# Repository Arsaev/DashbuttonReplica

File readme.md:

**Dashbutton Replica** 
its a open source replica of IoT wifi button from Amazon

PCB and circuit in Eagle Project format

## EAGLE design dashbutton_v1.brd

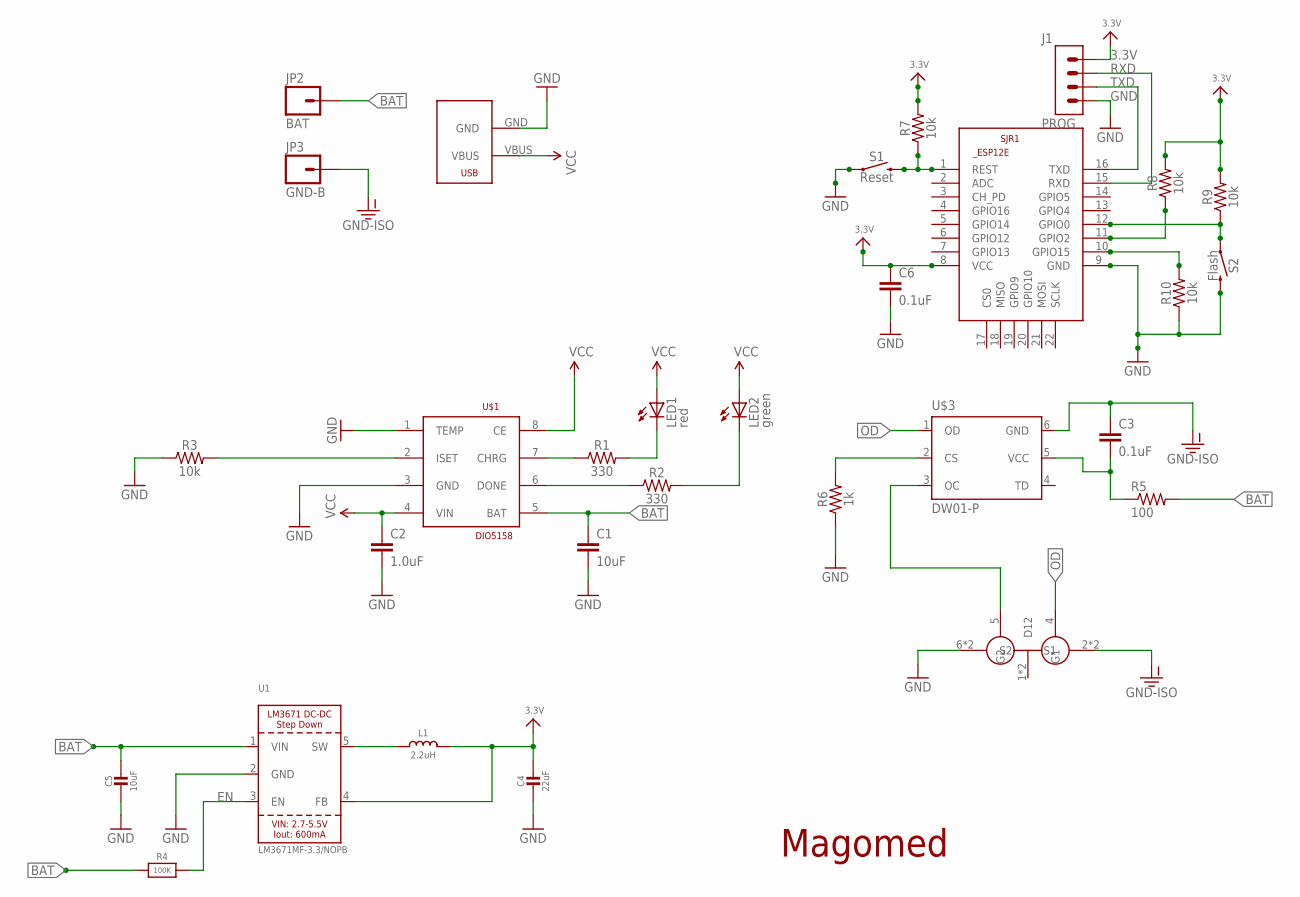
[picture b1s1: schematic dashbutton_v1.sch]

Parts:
C1: 10uF; 1206
C2: 1.0uF; 0603
C3, C6: 0.1uF; 0603
C4: 22uF; 0805-NO
C5: 10uF; 0805-NO
J1: PROG; 62000411121
JP2: BAT; 1X01
JP3: GND-B; 1X01
L1: 2.2uH; INDUCTOR_TAIYOYUDEN_NRH2412T
LED1: red; CHIP-LED0805
LED2: green; CHIP-LED0805
R1, R2: 330; 0603
R3, R7, R8, R9, R10: 10k; 0603
R4: 100K; 0805-NO
R5: 100; 0603-RES
R6: 1k; 0603
S1: Reset; TACTILE_SWITCH_SMD_6.2MM_TALL
S2: Flash; TACTILE_SWITCH_SMD_6.2MM_TALL
SJR1: ESP8266-12EESP12E; ESP8266-ESP12E
U1: LM3671MF-3.3/NOPB; SOT23-5
U$1: DIO5158; SOIC-8
U$3: DW01-P; SOT23-6L
U$4: FS8205A; TSSOP8
U$5: USB-MICROB-POWERONLY

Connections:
3.3V: C4.1, C6.1, J1.1, L1.2, R7.2, R8.2, R9.2, SJR1.8 (VCC), U1.4 (FB)
BAT: C1.1, C5.1, JP2.1, R4.1, R5.2, U1.1 (VIN), U$1.5 (BAT)
CHRG: R1.1, U$1.7 (CHRG)
DONE: R2.1, U$1.6 (DONE)
EN: R4.2, U1.3 (EN)
GND: C1.2, C2.2, C4.2, C5.2, C6.2, J1.4, R3.1, R6.1, R10.1, S1.A2 (1), S2.B2 (2), SJR1.9 (GND), U1.2 (GND), U$1.1 (TEMP), U$1.3 (GND), U$4.6 (S2), U$4.7 (S2), U$5.GND
GND-ISO: C3.1, JP3.1, U$3.6 (GND), U$4.2 (S1), U$4.3 (S1)
ISET: R3.2, U$1.2 (ISET)
LED1: LED1.C, R1.2
LED2: LED2.C, R2.2
unnamed: R6.2, U$3.2 (CS)
unnamed: U$3.3 (OC), U$4.5 (G2)
unnamed: L1.1, U1.5 (SW)
unnamed: R7.1, S1.B2 (2), SJR1.1 (REST)
unnamed: R9.1, S2.A2 (1), SJR1.12 (GPIO0)
unnamed: R10.2, SJR1.10 (GPIO15)
unnamed: R8.1, SJR1.11 (GPIO2)
OD: U$3.1 (OD), U$4.4 (G1)
RXD: J1.2, SJR1.15 (RXD)
TXD: J1.3, SJR1.16 (TXD)
VCC: C2.1, LED1.A, LED2.A, U$1.4 (VIN), U$1.8 (CE), U$5.VBUS
VCC-DW: C3.2, R5.1, U$3.5 (VCC)

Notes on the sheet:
Magomed

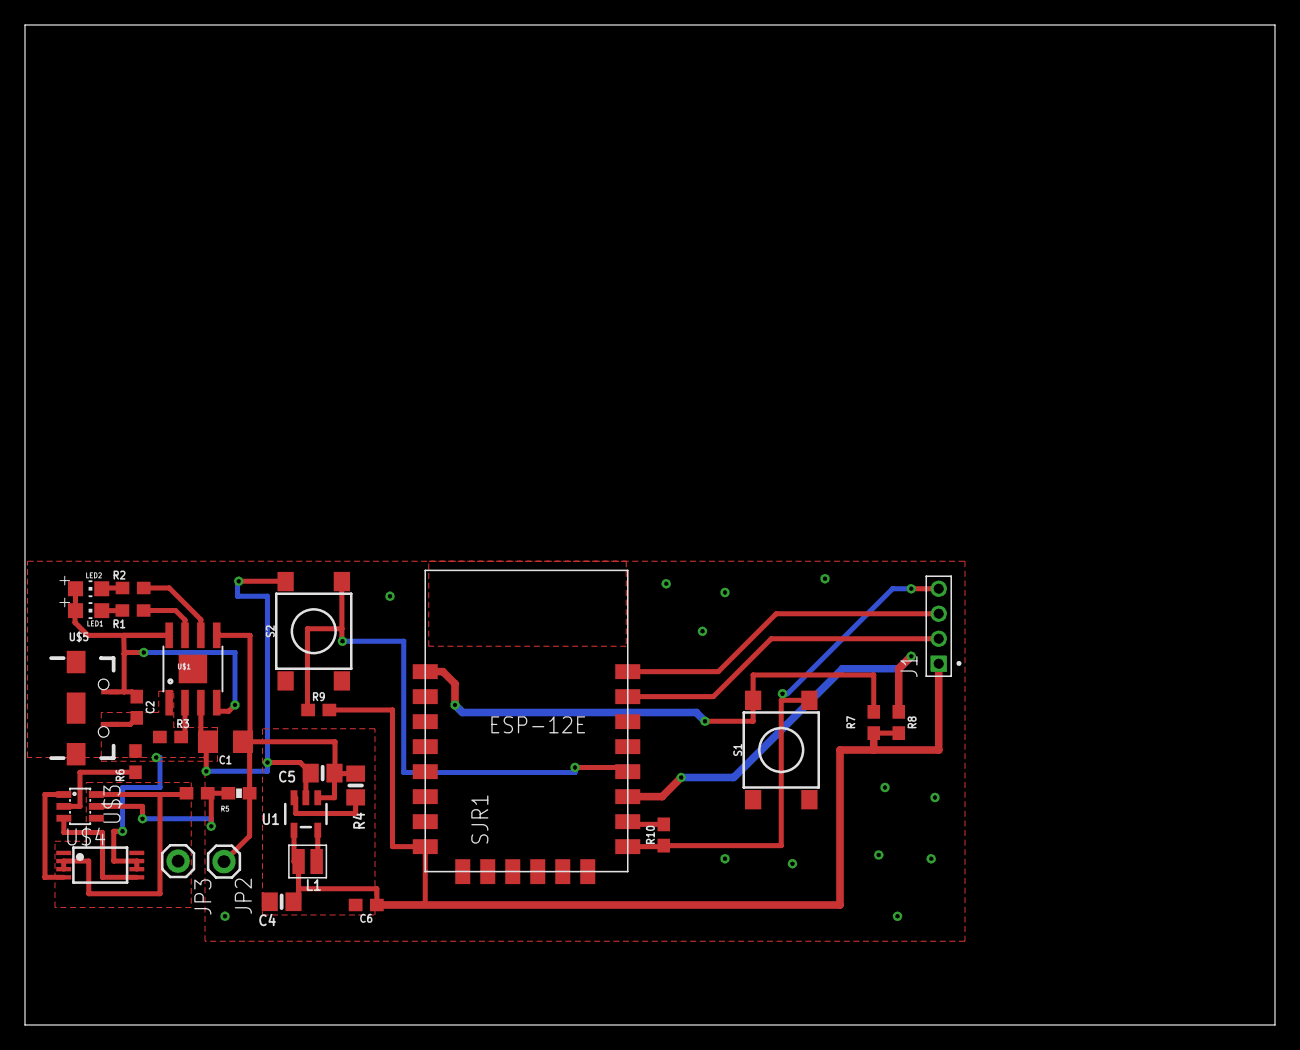
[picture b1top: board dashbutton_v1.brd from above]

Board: 2 copper layers, 100.0 x 80.0 mm, 30 parts (0 on the bottom side), 22 nets.

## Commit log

2019-06-16 readme.md

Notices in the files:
parts and their libraries:
SparkFun-Capacitors: Licensing: Creative Commons ShareAlike 4.0 International - https://creativecommons.org/licenses/by-sa/4.0
microbuilder: This work is placed in the public domain, and may be freely used for commercial and non-commercial work with the following conditions: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
